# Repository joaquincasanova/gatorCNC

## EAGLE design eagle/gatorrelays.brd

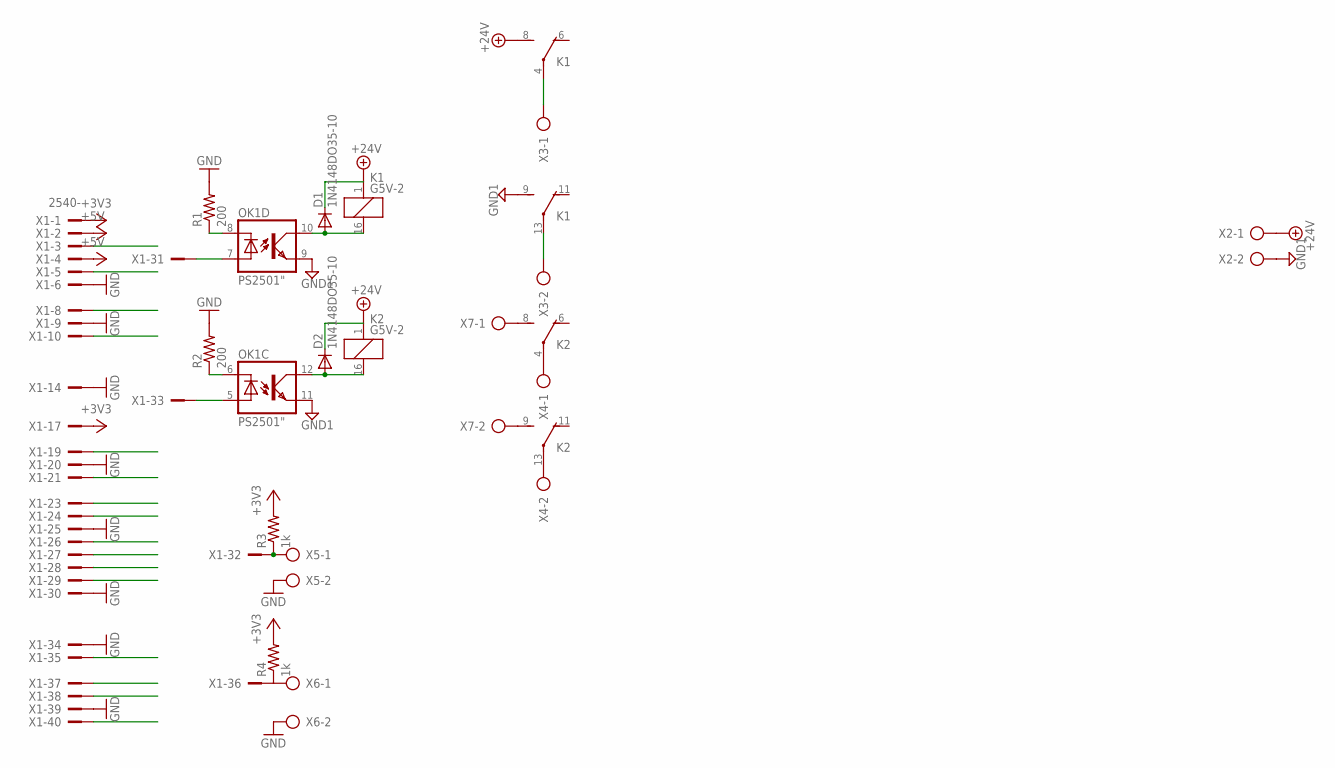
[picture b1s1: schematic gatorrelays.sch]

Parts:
D1, D2: 1N4148DO35-10; DO35-10
K1, K2: G5V-2
OK1: PS2501"; DIL16
R1, R2: 200; 0207/12
R3, R4: 1k; 0207/12
X1: 2540-; PAK100/2500-40
X2, X3, X4, X5, X6, X7: AK300/2

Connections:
+3V3: R3.2, R4.2, X1.1, X1.17
+5V: X1.2, X1.4
+24V: D1.C, D2.C, K1.1, K1.8 (S), K2.1, X2.1
GND: R1.2, R2.2, X1.6, X1.9, X1.14, X1.20, X1.25, X1.30, X1.34, X1.39, X5.2, X6.2
GND1: K1.9 (S), OK1.9 (EMI), OK1.11 (EMI), X2.2
GPIO5: X1.29
GPIO6: OK1.7 (A), X1.31
GPIO13: OK1.5 (A), X1.33
GPIO19: X1.35
GPIO20: X1.38
GPIO21: X1.40
GPIO26: X1.37
unnamed: OK1.8 (C), R1.1
unnamed: OK1.6 (C), R2.1
unnamed: R3.1, X1.32, X5.1
unnamed: D1.A, K1.16 (2), OK1.10 (COL)
unnamed: D2.A, K2.16 (2), OK1.12 (COL)
unnamed: K1.4, X3.1
unnamed: K1.13, X3.2
unnamed: K2.13, X4.2
unnamed: K2.4, X4.1
unnamed: K2.8 (S), X7.1
unnamed: K2.9 (S), X7.2

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
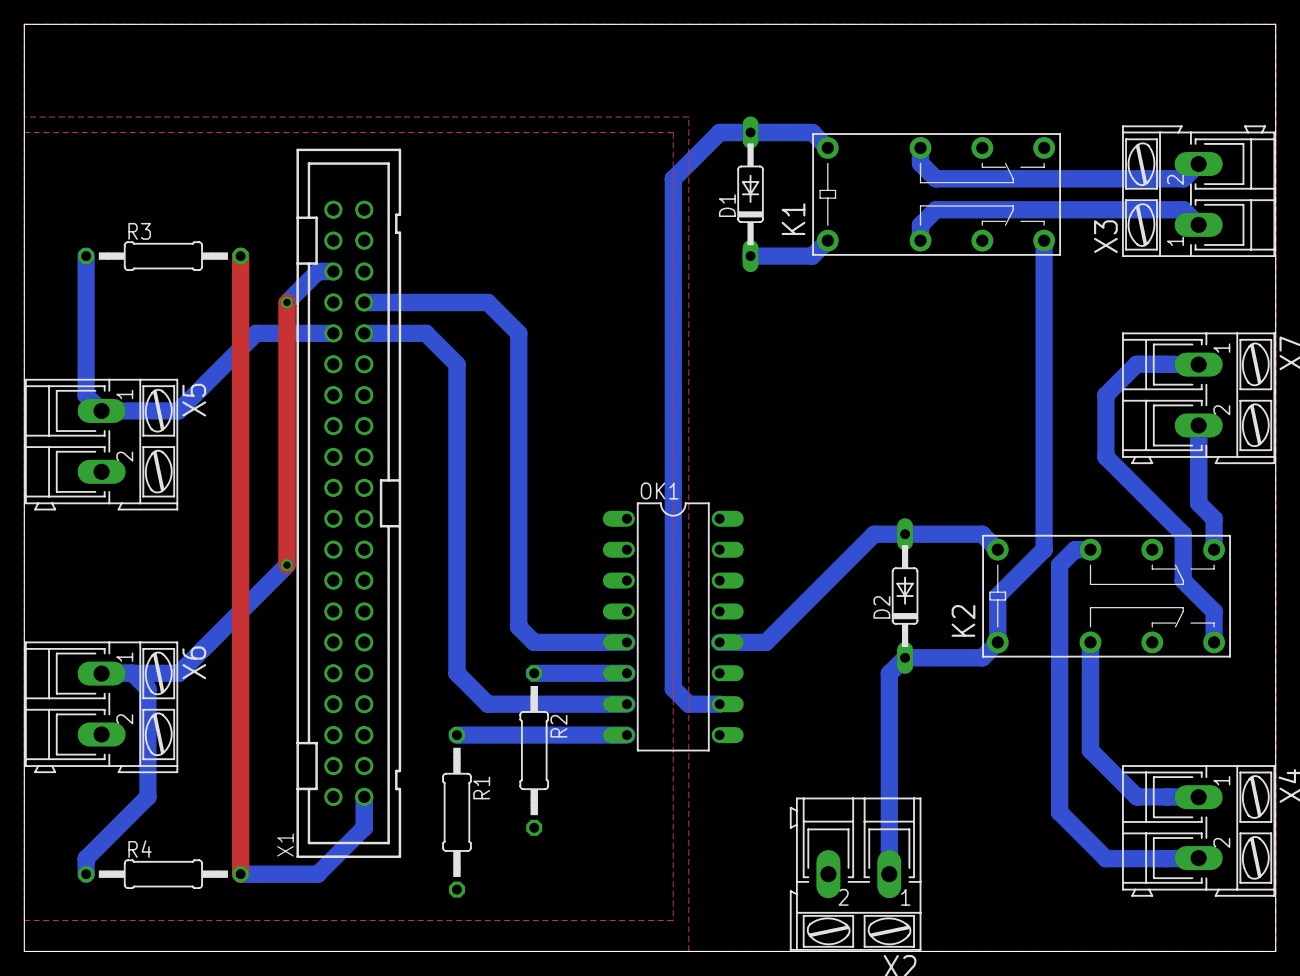
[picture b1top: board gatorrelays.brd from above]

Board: 2 copper layers, 102.9 x 76.2 mm, 16 parts (0 on the bottom side), 20 nets.

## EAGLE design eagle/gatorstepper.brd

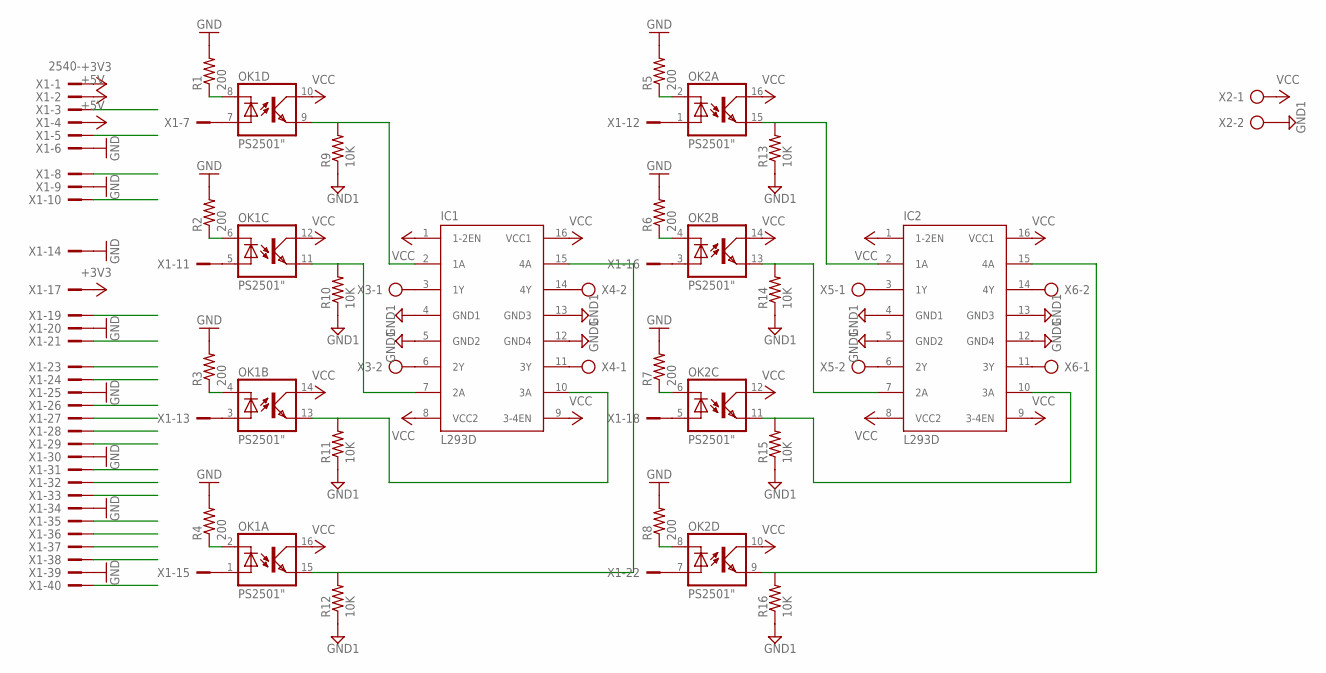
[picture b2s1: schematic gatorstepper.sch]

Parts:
IC1, IC2: L293D; DIL16
OK1, OK2: PS2501"; DIL16
R1, R2, R3, R4, R5, R6, R7, R8: 200; 0207/12
R9, R10, R11, R12, R13, R14, R15, R16: 10K; 0207/12
X1: 2540-; PAK100/2500-40
X2, X3, X4, X5, X6: AK300/2

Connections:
+3V3: X1.1, X1.17
+5V: X1.2, X1.4
GND: R1.2, R2.2, R3.2, R4.2, R5.2, R6.2, R7.2, R8.2, X1.6, X1.9, X1.14, X1.20, X1.25, X1.30, X1.34, X1.39
GND1: IC1.4 (GND1), IC1.5 (GND2), IC1.12 (GND4), IC1.13 (GND3), IC2.4 (GND1), IC2.5 (GND2), IC2.12 (GND4), IC2.13 (GND3), R9.1, R10.1, R11.1, R12.1, R13.1, R14.1, R15.1, R16.1, X2.2
GPIO5: X1.29
GPIO6: X1.31
GPIO12: X1.32
GPIO13: X1.33
GPIO16: X1.36
GPIO19: X1.35
GPIO20: X1.38
GPIO21: X1.40
GPIO26: X1.37
unnamed: OK1.8 (C), R1.1
unnamed: OK1.6 (C), R2.1
unnamed: OK1.4 (C), R3.1
unnamed: OK1.2 (C), R4.1
unnamed: OK2.2 (C), R5.1
unnamed: OK2.4 (C), R6.1
unnamed: OK2.6 (C), R7.1
unnamed: OK2.8 (C), R8.1
unnamed: IC1.2 (1A), OK1.9 (EMI), R9.2
unnamed: IC1.7 (2A), OK1.11 (EMI), R10.2
unnamed: IC1.10 (3A), OK1.13 (EMI), R11.2
unnamed: IC1.15 (4A), OK1.15 (EMI), R12.2
unnamed: IC2.2 (1A), OK2.15 (EMI), R13.2
unnamed: IC2.7 (2A), OK2.13 (EMI), R14.2
unnamed: IC2.10 (3A), OK2.11 (EMI), R15.2
unnamed: IC2.15 (4A), OK2.9 (EMI), R16.2
unnamed: IC1.3 (1Y), X3.1
unnamed: IC1.6 (2Y), X3.2
unnamed: IC1.14 (4Y), X4.2
unnamed: IC1.11 (3Y), X4.1
unnamed: IC2.3 (1Y), X5.1
unnamed: IC2.6 (2Y), X5.2
unnamed: IC2.11 (3Y), X6.1
unnamed: IC2.14 (4Y), X6.2
unnamed: OK1.1 (A), X1.15
unnamed: OK2.1 (A), X1.12
unnamed: OK2.3 (A), X1.16
unnamed: OK2.5 (A), X1.18
unnamed: OK2.7 (A), X1.22
unnamed: OK1.3 (A), X1.13
unnamed: OK1.5 (A), X1.11
unnamed: OK1.7 (A), X1.7
VCC: IC1.1 (1-2EN), IC1.8 (VCC2), IC1.9 (3-4EN), IC1.16 (VCC1), IC2.1 (1-2EN), IC2.8 (VCC2), IC2.9 (3-4EN), IC2.16 (VCC1), OK1.10 (COL), OK1.12 (COL), OK1.14 (COL), OK1.16 (COL), OK2.10 (COL), OK2.12 (COL), OK2.14 (COL), OK2.16 (COL), X2.1

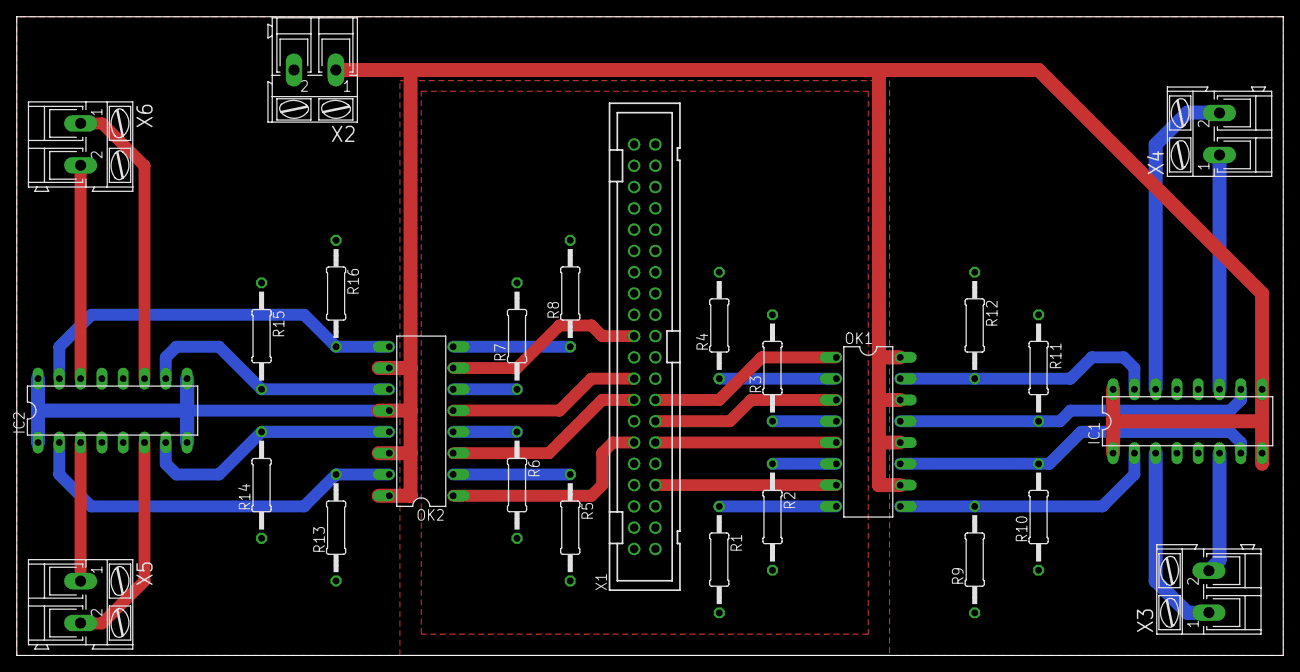
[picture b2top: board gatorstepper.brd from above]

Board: 2 copper layers, 151.1 x 76.2 mm, 26 parts (0 on the bottom side), 37 nets.

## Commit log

2015-07-18 direction check
2015-07-21 bresenham
2015-08-06 second commit
2015-09-22 layouts, bresenham
2015-09-30 gcode
2015-12-14 asdfg
